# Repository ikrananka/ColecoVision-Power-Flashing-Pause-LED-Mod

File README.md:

# ColecoVision Power/Flashing Pause LED Mod

## Introduction

This mod for the ColecoVision games console has two functions.  The first is to provide a continuously lit red power LED.  This LED will illuminate whenever the ColecoVision is turned on and not paused.  The second function is to provide a hardwired, physical switch, to pause operation of the ColecoVision allowing you to pause a game at any point and resume play at your leisure.  A unique feature of this mod is that when paused the power/pause LED flashes to indicate that the system is paused.  The rate of flashing is user adjustable from 0.6 to 3.3Hz.  When pause is turned off the flashing LED reverts to being continuously lit (until the system is either paused again or is turned off).
The pause function is achieved by pulling the WAIT line of the ColecoVision’s Z80 CPU low.  This in effect pauses all Z80 processing and therefore pauses the game you’re playing.  However, the audio is not paused and will continue to emit the last note/tone which can be very annoying.  Therefore, this mod not only pauses the Z80 processor but also disconnects the audio output whenever pause is engaged.

The Finished Product

## FAQ

Q.	Will this work with Super Game Module (SGM1) games?

A.	Yes (if you wire the audio as recommended later in this document).  All SGM enhanced games still use the Z80 processor and so they will pause when the Z80 is paused just like any other ColecoVision game.  However, SGM enhanced audio is fed to the ColecoVision via the expansion port (EXAUD), bypassing the ColecoVision’s onboard sound from the SN76489A.  Therefore, it is important that when paused, audio is disconnected from a location after the point where audio from the SN76489A and EXAUD combine.  This is easy to do and instructions for this are provided later in this document.

Q.	Will this work with the upcoming Super Game Module 2 (SGM2)?

A.	Yes and No.  According to the latest information from Opcode Games, the SGM2 will be backwards compatible with SGM1 games and the pause mod will function in the same way as described in the answer above.  However, SGM2 specific games will use the new Z80 and/or 16-bit CPUs that are contained in the SGM2 unit and these cannot be paused using this mod.  However, Opcode Games has stated that “pause will be implemented in software for these games because of the dual CPU design” and so a hardware pause solution is not needed.  You never know, perhaps Opcode Games will make the SGM2s power LED flash when a game is paused!!!

Q.	Does this work with the Expansion Module #1?

A.	No.  The expansion module #1 uses its own processor and audio chip and like the SGM2 cannot be paused by this mod.  Be aware that moving the pause switch to the pause position while playing an expansion module #1 game may disconnect the audio so leave the switch in the normal position when playing these games.

Q.	Is the mod reversable?

A.	The mod is mostly reversable other than the fact that you must drill two large holes in the ColecoVision’s top housing.  These holes are obviously not reversable.

Q. Can the top and bottom halves of the ColecoVision console shell be separated during system maintenance/troubleshooting?

A. Yes.  A pair of 6-pin Molex connectors ae included in the design that when disconnected from each other allow the top and bottom halves of the ColecoVision console shell to be completely separated from each other.

Q.	Can the switch and circuit board be removed for maintenance/troubleshooting?

A.	Yes.  Assuming you don’t use any glue during the installation, which isn’t necessary, then the switch and circuit board can be easily removed.

## The Kit
 
The installation kit contains the following items:
1.	ColecoVision Power/Pause LED Mod PCB.
2.	Motherboard wiring harness.
3.	Pause switch wiring harness (includes pause switch).
4.	Circuit board custom spacer.
5.	Pause switch nut (used to hold switch and circuit board in place).
6.	LED holder.

## Bill of Materials

Please download and refer to the [Bill of Materials](https://github.com/ikrananka/ColecoVision-Power-Flashing-Pause-LED-Mod/blob/main/Bill%20of%20Materials%20v1.0.pdf) contained in this repository.

## Printed Circuit Board

Included in this repository are the PCB schematic and board files created using Eagle v9.1.0.  I have also included Gerber files that are suitable for ordering PCBs from [JLCPCB](https://jlcpcb.com).  If you plan on ordering boards from other PCB manufacturers then you may need to create new gerber files that adhere to that manufacturer's requirements.

### LED Installation

Note that the LED should be soldered onto the underside of the PCB, i.e. the opposite side to all of the other components.  Critically, the LED **MUST** be slightly raised by 0.75mm (30 thou) above the PCB surface as shown below.  I use small pieces of plastic card (0.75mm thick) to do this, held in place with sticky tack, and then solder the LED in place.  Don't forget to remove the pieces of plastic after soldering the LED.

## Construction of the Wiring Harnesses
### Tools Needed

- Soldering iron and solder
- Wire cutter
- Wire stripper
- Crimping tool (I use a [Waldom W-HT-1921 crimping tool](https://www.digikey.com/en/products/detail/gc-electronics/W-HT-1921/26396)).

### Wire

Note that my preference is to use multistrand (7/32) 24AWG wire for this kit.  Nevertheless, 22AWG multistrand wire would also likely work fine.

### Wire Lengths and Connections

Refer to the following wiring diagram and photographs for details.  Use the appropriate crimps (from the Bill of Materials) for wires that are part of the Molex connectors.  I recommend soldering the wires to the four connections on the back of the rocker switch.

## The Custom Spacer

The custom spacer provides support under the PCB when tightening the nut that holds the rocker switch and PCB in place.  It is simply a 3D printed circular spacer/washer with the following dimensions:

- ID = 20.5mm
- OD = 26.5mm
- Thickness = 3mm

You can either download the design from [thingiverse.com](https://www.thingiverse.com/thing:3446247) or from the ["Custom_Spacer.zip"](Custom_Spacer.zip) file included in this repository.

## The Pause Switch Nut

The pause switch nut is included with the purchase of the Radio Shack DPDT switch from the bill of materials.  However, the nut needs to be modified slightly by lightly sanding down the ridges that will press against the PCB when installed.  To do this I typically use 300 grit sandpaper face up on a flat surface and hold the nut with the ridges flat against the sandpaper.  I then slide the nut over the sandpaper in a circular motion while pressing down.  The photo below shows the nut before and after and should give you a good idea of how much of the ridges you need to sand down.  Note that if you don't sand down these ridges then you will find that you won't be able to screw the nut onto the switch when it is installed in the ColecoVision with the spacer and PCB installed.  Sanding down the ridges allows the nut to get close enough to the thread on the switch so that it can be tightened up.

## Installation Instructions

Refer to the [installation instructions pdf](https://github.com/ikrananka/ColecoVision-Power-Flashing-Pause-LED-Mod/blob/main/Installation%20Instructions%20v1.1.pdf) included with this repository.

## Pause Flashing Frequency

The installation instructions include details of how to adjust the flashing frequency.  I have also provided a video to illustrate what different flashing frequncies look like.  You can view the video [here](https://youtu.be/l38Kgi8KPcs).

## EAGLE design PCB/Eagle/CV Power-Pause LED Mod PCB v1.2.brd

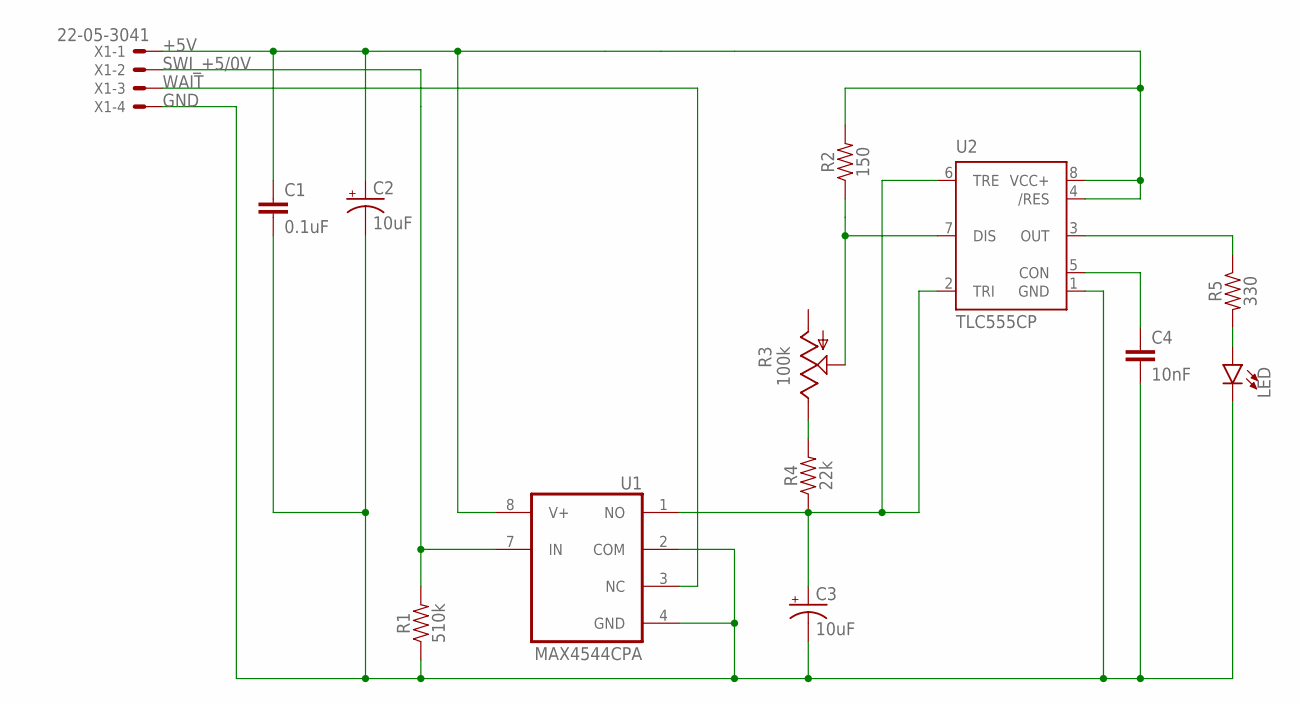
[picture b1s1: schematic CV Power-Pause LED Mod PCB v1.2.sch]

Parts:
C1: 0.1uF; CAP-PTH-SMALL2
C2, C3: 10uF; E2,5-6
C4: 10nF; CAP-PTH-SMALL2
LED: LED5MM; LED_5MM
R1: 510k; AXIAL-0.3
R2: 150; AXIAL-0.3
R3: 100k; CT6
R4: 22k; AXIAL-0.3
R5: 330; AXIAL-0.3
U1: MAX4544CPA; DIP08
U2: TLC555CP; DIP08
X1: 22-05-3041

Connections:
+5V: C1.1, C2.+, R2.P$2 (2), U1.8 (V+), U2.4 (/RES), U2.8 (VCC+), X1.1
GND: C1.2, C2.-, C3.-, C4.2, LED.K (C), R1.P$1 (1), U1.2 (COM), U1.4 (GND), U2.1 (GND), X1.4
unnamed: LED.A, R5.P$2 (2)
unnamed: C4.1, U2.5 (CON)
unnamed: R2.P$1 (1), R3.S, U2.7 (DIS)
unnamed: R5.P$1 (1), U2.3 (OUT)
unnamed: R3.E, R4.P$2 (2)
unnamed: C3.+, R4.P$1 (1), U1.1 (NO), U2.2 (TRI), U2.6 (TRE)
SWI_+5/0V: R1.P$2 (2), U1.7 (IN), X1.2
WAIT: U1.3 (NC), X1.3

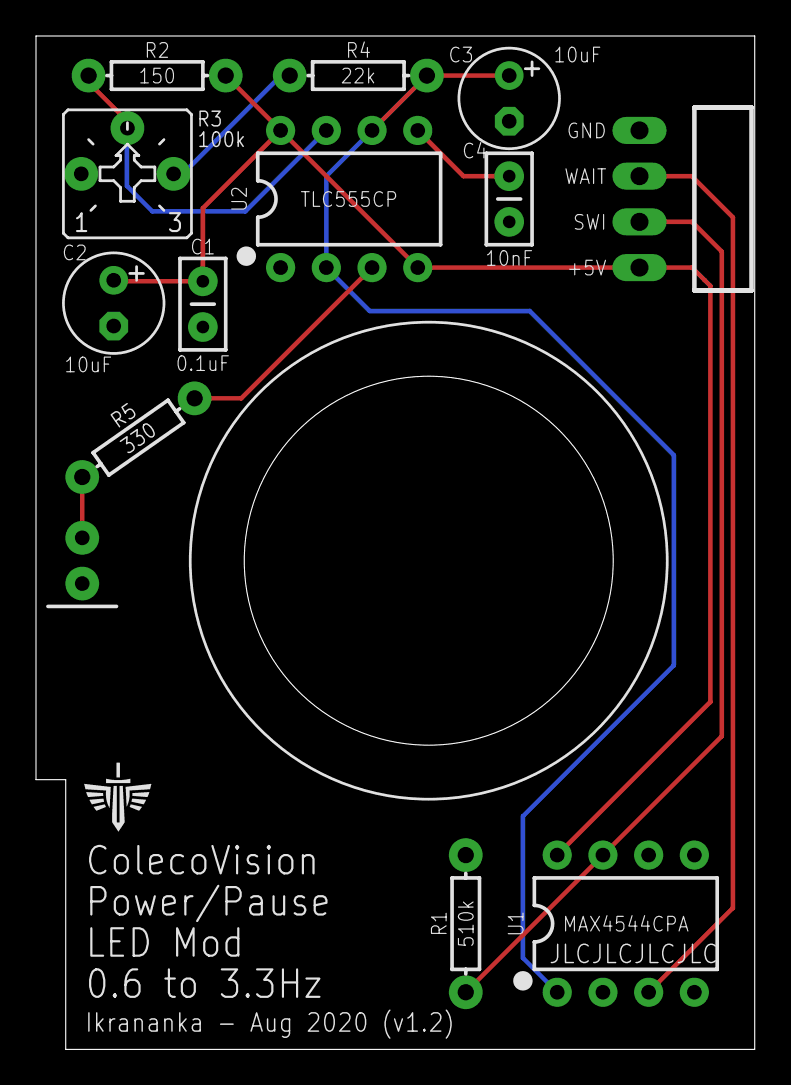
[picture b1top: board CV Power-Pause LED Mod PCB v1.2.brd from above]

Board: 2 copper layers, 39.9 x 56.3 mm, 13 parts (1 on the bottom side), 10 nets.

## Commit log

2021-04-22 Update LICENSE
2021-05-03 Create delete

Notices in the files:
parts and their libraries:
SparkFun-Capacitors: Licensing: CC v3.0 Share-Alike You are welcome to use this library for commercial purposes.
SparkFun-LED: Licensing: Creative Commons ShareAlike 4.0 International - https://creativecommons.org/licenses/by-sa/4.0
